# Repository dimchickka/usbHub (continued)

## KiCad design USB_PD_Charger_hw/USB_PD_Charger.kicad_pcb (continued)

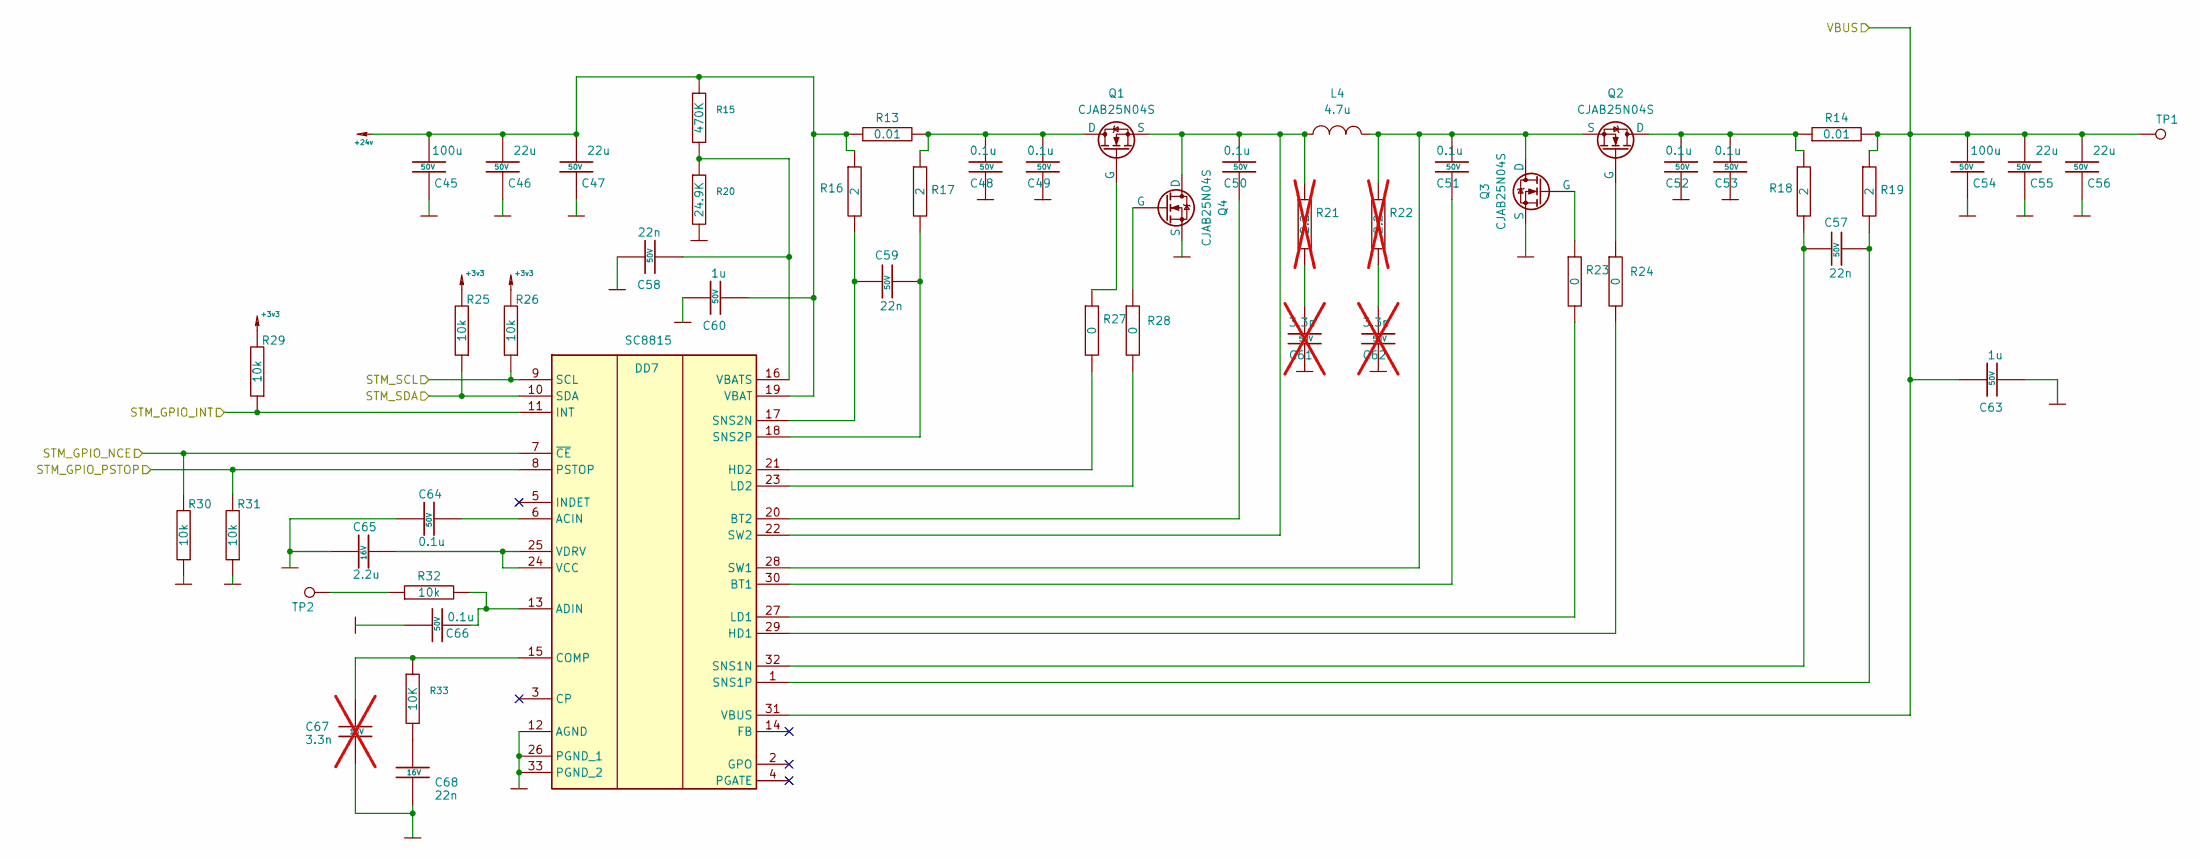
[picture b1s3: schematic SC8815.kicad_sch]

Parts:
C45, C54: 100u; CP_Elec_10x10.5_Pad2Plus; Tolerance 20%; Voltage 50V
C46, C47, C55, C56: 22u; CP_Elec_6.3x5.8_Pad2Plus; Tolerance 20%; Voltage 50V
C48, C49, C50, C51, C52, C53, C64, C66: 0.1u; CAP_0603_Silks; Tolerance 10%; Voltage 50V
C57, C58, C59: 22n; CAP_0603_Silks; Tolerance 5%; Voltage 50V
C60, C63: 1u; CAP_0603_Silks; Tolerance 10%; Voltage 50V
C61, C62: 3.3n; CAP_0603_Silks; Tolerance 10%; Voltage 50V; not fitted
C65: 2.2u; CAP_0603_Silks; Tolerance 10%; Voltage 16V
C67: 3.3n; CAP_0603_Silks; Tolerance 10%; Voltage 16V; not fitted
C68: 22n; CAP_0603_Silks; Tolerance 5%; Voltage 16V
DD7: SC8815; QFN40P400X400X80-33N-D; Manufacturer_Part_Number SC8815
L4: 4.7u; L_TaiTech_TMPC1265_13.5x12.5mm; Tolerance 20%
Q1, Q2, Q3, Q4: CJAB25N04S; CJAB25N04S_PDFNWB3.3x3.3-8L
R13, R14: 0.01; R_0805_2012Metric; Tolerance 1%
R15: 470K; RES_0603_Silks
R16, R17, R18, R19: 2; RES_0603_Silks; Tolerance 1%
R20: 24.9K; RES_0603_Silks
R21, R22: 2.2; RES_0603_Silks; Tolerance 1%; not fitted
R23, R24, R27, R28: 0; RES_0603_Silks; Tolerance 1%
R25, R26, R29, R30, R31, R32: 10k; RES_0603_Silks; Tolerance 1%
R33: 10K; RES_0603_Silks
TP1, TP2: TestPoint; TestPoint_Pad_D2.0mm

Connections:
+3v3: R25.2, R26.2, R29.2; also elsewhere on the board
+24v: C45.2, C46.2, C47.2, C60.2, DD7.19 (VBAT), R13.1, R15.1, R16.1; also elsewhere on the board
/Dual_USB_C_ports_1/STM_GPIO_INT1: DD7.11 (INT), R29.1; also elsewhere on the board
/Dual_USB_C_ports_1/STM_GPIO_NCE1: DD7.7 (~CE), R30.2; also elsewhere on the board
/Dual_USB_C_ports_1/STM_GPIO_PSTOP1: DD7.8 (PSTOP), R31.2; also elsewhere on the board
/Dual_USB_C_ports_1/STM_SCL1: DD7.9 (SCL), R26.1; also elsewhere on the board
/Dual_USB_C_ports_1/STM_SDA1: DD7.10 (SDA), R25.1; also elsewhere on the board
/Dual_USB_C_ports_1/VBUS_USB_CON_1: C54.2, C55.2, C56.2, C63.1, DD7.31 (VBUS), R14.2, R19.1, TP1.1; also elsewhere on the board
GND: C45.1, C46.1, C47.1, C48.2, C49.2, C52.2, C53.2, C54.1, C55.1, C56.1, C58.1, C60.1, C61.2, C62.2, C63.2, C64.2, C65.2, C66.1, C67.2, C68.2, DD7.12 (AGND), DD7.26 (PGND_1), DD7.33 (PGND_2), Q3.3 (S), Q4.3 (S), R20.2, R30.1, R31.1; also elsewhere on the board
unnamed: C61.1, R21.2
unnamed: C62.1, R22.2
unnamed: C68.1, R33.2
unnamed: C64.1, DD7.6 (ACIN)
unnamed: C66.2, DD7.13 (ADIN), R32.2
unnamed: C51.2, DD7.30 (BT1)
unnamed: C50.2, DD7.20 (BT2)
unnamed: C67.1, DD7.15 (COMP), R33.1
unnamed: DD7.29 (HD1), R24.2
unnamed: DD7.21 (HD2), R27.2
unnamed: DD7.27 (LD1), R23.2
unnamed: DD7.23 (LD2), R28.2
unnamed: C57.2, DD7.32 (SNS1N), R18.2
unnamed: C57.1, DD7.1 (SNS1P), R19.2
unnamed: C59.2, DD7.17 (SNS2N), R16.2
unnamed: C59.1, DD7.18 (SNS2P), R17.2
unnamed: C51.1, DD7.28 (SW1), L4.1, Q2.3 (S), Q3.1 (D), R22.1
unnamed: C50.1, DD7.22 (SW2), L4.2, Q1.3 (S), Q4.1 (D), R21.1
unnamed: C58.2, DD7.16 (VBATS), R15.2, R20.1
unnamed: C65.1, DD7.24 (VCC), DD7.25 (VDRV)
unnamed: C48.1, C49.1, Q1.1 (D), R13.2, R17.1
unnamed: Q1.2 (G), R27.1
unnamed: C52.1, C53.1, Q2.1 (D), R14.1, R18.1
unnamed: Q2.2 (G), R24.1
unnamed: Q3.2 (G), R23.1
unnamed: Q4.2 (G), R28.1
unnamed: R32.1, TP2.1

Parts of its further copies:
C69, C78, C95, C104, C119, C128, C145, C154, C169, C178, C195, C204, C219, C228, C245, C254, C269, C278, C295, C304, C319, C328, C345, C354, C369, C378, C395, C404, C419, C428, C445, C454, C469, C478, C495, C504, C519, C528: 100u; CP_Elec_10x10.5_Pad2Plus; Tolerance 20%; Voltage 50V
C70, C71, C79, C80, C96, C97, C105, C106, C120, C121, C129, C130, C146, C147, C155, C156, C170, C171, C179, C180, C196, C197, C205, C206, C220, C221, C229, C230, C246, C247, C255, C256, C270, C271, C279, C280, C296, C297, C305, C306, C320, C321, C329, C330, C346, C347, C355, C356, C370, C371, C379, C380, C396, C397, C405, C406, C420, C421, C429, C430, C446, C447, C455, C456, C470, C471, C479, C480, C496, C497, C505, C506, C520, C521, C529, C530: 22u; CP_Elec_6.3x5.8_Pad2Plus; Tolerance 20%; Voltage 50V
C72, C73, C74, C75, C76, C77, C88, C90, C98, C99, C100, C101, C102, C103, C114, C116, C122, C123, C124, C125, C126, C127, C138, C140, C148, C149, C150, C151, C152, C153, C164, C166, C172, C173, C174, C175, C176, C177, C188, C190, C198, C199, C200, C201, C202, C203, C214, C216, C222, C223, C224, C225, C226, C227, C238, C240, C248, C249, C250, C251, C252, C253, C264, C266, C272, C273, C274, C275, C276, C277, C288, C290, C298, C299, C300, C301, C302, C303, C314, C316, C322, C323, C324, C325, C326, C327, C338, C340, C348, C349, C350, C351, C352, C353, C364, C366, C372, C373, C374, C375, C376, C377, C388, C390, C398, C399, C400, C401, C402, C403, C414, C416, C422, C423, C424, C425, C426, C427, C438, C440, C448, C449, C450, C451, C452, C453, C464, C466, C472, C473, C474, C475, C476, C477, C488, C490, C498, C499, C500, C501, C502, C503, C514, C516, C522, C523, C524, C525, C526, C527, C538, C540: 0.1u; CAP_0603_Silks; Tolerance 10%; Voltage 50V
C81, C82, C83, C107, C108, C109, C131, C132, C133, C157, C158, C159, C181, C182, C183, C207, C208, C209, C231, C232, C233, C257, C258, C259, C281, C282, C283, C307, C308, C309, C331, C332, C333, C357, C358, C359, C381, C382, C383, C407, C408, C409, C431, C432, C433, C457, C458, C459, C481, C482, C483, C507, C508, C509, C531, C532, C533: 22n; CAP_0603_Silks; Tolerance 5%; Voltage 50V
C84, C87, C110, C113, C134, C137, C160, C163, C184, C187, C210, C213, C234, C237, C260, C263, C284, C287, C310, C313, C334, C337, C360, C363, C384, C387, C410, C413, C434, C437, C460, C463, C484, C487, C510, C513, C534, C537: 1u; CAP_0603_Silks; Tolerance 10%; Voltage 50V
C85, C86, C111, C112, C135, C136, C161, C162, C185, C186, C211, C212, C235, C236, C261, C262, C285, C286, C311, C312, C335, C336, C361, C362, C385, C386, C411, C412, C435, C436, C461, C462, C485, C486, C511, C512, C535, C536: 3.3n; CAP_0603_Silks; Tolerance 10%; Voltage 50V; not fitted
C89, C115, C139, C165, C189, C215, C239, C265, C289, C315, C339, C365, C389, C415, C439, C465, C489, C515, C539: 2.2u; CAP_0603_Silks; Tolerance 10%; Voltage 16V
C91, C117, C141, C167, C191, C217, C241, C267, C291, C317, C341, C367, C391, C417, C441, C467, C491, C517, C541: 3.3n; CAP_0603_Silks; Tolerance 10%; Voltage 16V; not fitted
C92, C118, C142, C168, C192, C218, C242, C268, C292, C318, C342, C368, C392, C418, C442, C468, C492, C518, C542: 22n; CAP_0603_Silks; Tolerance 5%; Voltage 16V
DD8, DD12, DD13, DD17, DD18, DD22, DD23, DD27, DD28, DD32, DD33, DD37, DD38, DD42, DD43, DD47, DD48, DD52, DD53: SC8815; QFN40P400X400X80-33N-D; Manufacturer_Part_Number SC8815
L5, L6, L7, L8, L9, L10, L11, L12, L13, L14, L15, L16, L17, L18, L19, L20, L21, L22, L23: 4.7u; L_TaiTech_TMPC1265_13.5x12.5mm; Tolerance 20%
Q5, Q6, Q7, Q8, Q9, Q10, Q11, Q12, Q13, Q14, Q15, Q16, Q17, Q18, Q19, Q20, Q21, Q22, Q23, Q24, Q25, Q26, Q27, Q28, Q29, Q30, Q31, Q32, Q33, Q34, Q35, Q36, Q37, Q38, Q39, Q40, Q41, Q42, Q43, Q44, Q45, Q46, Q47, Q48, Q49, Q50, Q51, Q52, Q53, Q54, Q55, Q56, Q57, Q58, Q59, Q60, Q61, Q62, Q63, Q64, Q65, Q66, Q67, Q68, Q69, Q70, Q71, Q72, Q73, Q74, Q75, Q76, Q77, Q78, Q79, Q80: CJAB25N04S; CJAB25N04S_PDFNWB3.3x3.3-8L
R34, R35, R57, R58, R78, R79, R101, R102, R122, R123, R145, R146, R166, R167, R189, R190, R210, R211, R233, R234, R254, R255, R277, R278, R298, R299, R321, R322, R342, R343, R365, R366, R386, R387, R409, R410, R430, R431: 0.01; R_0805_2012Metric; Tolerance 1%
R36, R59, R80, R103, R124, R147, R168, R191, R212, R235, R256, R279, R300, R323, R344, R367, R388, R411, R432: 470K; RES_0603_Silks
R37, R38, R39, R40, R60, R61, R62, R63, R81, R82, R83, R84, R104, R105, R106, R107, R125, R126, R127, R128, R148, R149, R150, R151, R169, R170, R171, R172, R192, R193, R194, R195, R213, R214, R215, R216, R236, R237, R238, R239, R257, R258, R259, R260, R280, R281, R282, R283, R301, R302, R303, R304, R324, R325, R326, R327, R345, R346, R347, R348, R368, R369, R370, R371, R389, R390, R391, R392, R412, R413, R414, R415, R433, R434, R435, R436: 2; RES_0603_Silks; Tolerance 1%
R41, R64, R85, R108, R129, R152, R173, R196, R217, R240, R261, R284, R305, R328, R349, R372, R393, R416, R437: 24.9K; RES_0603_Silks
R42, R43, R65, R66, R86, R87, R109, R110, R130, R131, R153, R154, R174, R175, R197, R198, R218, R219, R241, R242, R262, R263, R285, R286, R306, R307, R329, R330, R350, R351, R373, R374, R394, R395, R417, R418, R438, R439: 2.2; RES_0603_Silks; Tolerance 1%; not fitted
R44, R45, R48, R49, R67, R68, R71, R72, R88, R89, R92, R93, R111, R112, R115, R116, R132, R133, R136, R137, R155, R156, R159, R160, R176, R177, R180, R181, R199, R200, R203, R204, R220, R221, R224, R225, R243, R244, R247, R248, R264, R265, R268, R269, R287, R288, R291, R292, R308, R309, R312, R313, R331, R332, R335, R336, R352, R353, R356, R357, R375, R376, R379, R380, R396, R397, R400, R401, R419, R420, R423, R424, R440, R441, R444, R445: 0; RES_0603_Silks; Tolerance 1%
R46, R47, R50, R51, R52, R53, R69, R70, R73, R74, R75, R76, R90, R91, R94, R95, R96, R97, R113, R114, R117, R118, R119, R120, R134, R135, R138, R139, R140, R141, R157, R158, R161, R162, R163, R164, R178, R179, R182, R183, R184, R185, R201, R202, R205, R206, R207, R208, R222, R223, R226, R227, R228, R229, R245, R246, R249, R250, R251, R252, R266, R267, R270, R271, R272, R273, R289, R290, R293, R294, R295, R296, R310, R311, R314, R315, R316, R317, R333, R334, R337, R338, R339, R340, R354, R355, R358, R359, R360, R361, R377, R378, R381, R382, R383, R384, R398, R399, R402, R403, R404, R405, R421, R422, R425, R426, R427, R428, R442, R443, R446, R447, R448, R449: 10k; RES_0603_Silks; Tolerance 1%
R54, R77, R98, R121, R142, R165, R186, R209, R230, R253, R274, R297, R318, R341, R362, R385, R406, R429, R450: 10K; RES_0603_Silks
TP3, TP4, TP5, TP6, TP7, TP8, TP9, TP10, TP11, TP12, TP13, TP14, TP15, TP16, TP17, TP18, TP19, TP20, TP21, TP22, TP23, TP24, TP25, TP26, TP27, TP28, TP29, TP30, TP31, TP32, TP33, TP34, TP35, TP36, TP37, TP38, TP39, TP40: TestPoint; TestPoint_Pad_D2.0mm

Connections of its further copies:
+3v3: R46.2, R47.2, R50.2, R69.2, R70.2, R73.2, R90.2, R91.2, R94.2, R113.2, R114.2, R117.2, R134.2, R135.2, R138.2, R157.2, R158.2, R161.2, R178.2, R179.2, R182.2, R201.2, R202.2, R205.2, R222.2, R223.2, R226.2, R245.2, R246.2, R249.2, R266.2, R267.2, R270.2, R289.2, R290.2, R293.2, R310.2, R311.2, R314.2, R333.2, R334.2, R337.2, R354.2, R355.2, R358.2, R377.2, R378.2, R381.2, R398.2, R399.2, R402.2, R421.2, R422.2, R425.2, R442.2, R443.2, R446.2; also elsewhere on the board
+24v: C69.2, C70.2, C71.2, C84.2, C95.2, C96.2, C97.2, C110.2, C119.2, C120.2, C121.2, C134.2, C145.2, C146.2, C147.2, C160.2, C169.2, C170.2, C171.2, C184.2, C195.2, C196.2, C197.2, C210.2, C219.2, C220.2, C221.2, C234.2, C245.2, C246.2, C247.2, C260.2, C269.2, C270.2, C271.2, C284.2, C295.2, C296.2, C297.2, C310.2, C319.2, C320.2, C321.2, C334.2, C345.2, C346.2, C347.2, C360.2, C369.2, C370.2, C371.2, C384.2, C395.2, C396.2, C397.2, C410.2, C419.2, C420.2, C421.2, C434.2, C445.2, C446.2, C447.2, C460.2, C469.2, C470.2, C471.2, C484.2, C495.2, C496.2, C497.2, C510.2, C519.2, C520.2, C521.2, C534.2, DD8.19 (VBAT), DD12.19 (VBAT), DD13.19 (VBAT), DD17.19 (VBAT), DD18.19 (VBAT), DD22.19 (VBAT), DD23.19 (VBAT), DD27.19 (VBAT), DD28.19 (VBAT), DD32.19 (VBAT), DD33.19 (VBAT), DD37.19 (VBAT), DD38.19 (VBAT), DD42.19 (VBAT), DD43.19 (VBAT), DD47.19 (VBAT), DD48.19 (VBAT), DD52.19 (VBAT), DD53.19 (VBAT), R34.1, R36.1, R37.1, R57.1, R59.1, R60.1, R78.1, R80.1, R81.1, R101.1, R103.1, R104.1, R122.1, R124.1, R125.1, R145.1, R147.1, R148.1, R166.1, R168.1, R169.1, R189.1, R191.1, R192.1, R210.1, R212.1, R213.1, R233.1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; also elsewhere on the board
/Dual_USB_C_ports_1/STM_GPIO_INT2: DD8.11 (INT), R50.1; also elsewhere on the board
/Dual_USB_C_ports_1/STM_GPIO_NCE2: DD8.7 (~CE), R51.2; also elsewhere on the board
/Dual_USB_C_ports_1/STM_GPIO_PSTOP2: DD8.8 (PSTOP), R52.2; also elsewhere on the board
/Dual_USB_C_ports_1/STM_SCL2: DD8.9 (SCL), R47.1; also elsewhere on the board
/Dual_USB_C_ports_1/STM_SDA2: DD8.10 (SDA), R46.1; also elsewhere on the board
/Dual_USB_C_ports_1/VBUS_USB_CON_2: C78.2, C79.2, C80.2, C87.1, DD8.31 (VBUS), R35.2, R40.1, TP3.1; also elsewhere on the board
/Dual_USB_C_ports_2/STM_GPIO_INT1: DD12.11 (INT), R73.1; also elsewhere on the board
/Dual_USB_C_ports_2/STM_GPIO_INT2: DD13.11 (INT), R94.1; also elsewhere on the board
/Dual_USB_C_ports_2/STM_GPIO_NCE1: DD12.7 (~CE), R74.2; also elsewhere on the board
/Dual_USB_C_ports_2/STM_GPIO_NCE2: DD13.7 (~CE), R95.2; also elsewhere on the board
/Dual_USB_C_ports_2/STM_GPIO_PSTOP1: DD12.8 (PSTOP), R75.2; also elsewhere on the board
/Dual_USB_C_ports_2/STM_GPIO_PSTOP2: DD13.8 (PSTOP), R96.2; also elsewhere on the board
/Dual_USB_C_ports_2/STM_SCL1: DD12.9 (SCL), R70.1; also elsewhere on the board
/Dual_USB_C_ports_2/STM_SCL2: DD13.9 (SCL), R91.1; also elsewhere on the board
/Dual_USB_C_ports_2/STM_SDA1: DD12.10 (SDA), R69.1; also elsewhere on the board
/Dual_USB_C_ports_2/STM_SDA2: DD13.10 (SDA), R90.1; also elsewhere on the board
/Dual_USB_C_ports_2/VBUS_USB_CON_1: C104.2, C105.2, C106.2, C113.1, DD12.31 (VBUS), R58.2, R63.1, TP5.1; also elsewhere on the board
/Dual_USB_C_ports_2/VBUS_USB_CON_2: C128.2, C129.2, C130.2, C137.1, DD13.31 (VBUS), R79.2, R84.1, TP7.1; also elsewhere on the board
/Dual_USB_C_ports_3/STM_GPIO_INT1: DD17.11 (INT), R117.1; also elsewhere on the board
/Dual_USB_C_ports_3/STM_GPIO_INT2: DD18.11 (INT), R138.1; also elsewhere on the board
/Dual_USB_C_ports_3/STM_GPIO_NCE1: DD17.7 (~CE), R118.2; also elsewhere on the board
/Dual_USB_C_ports_3/STM_GPIO_NCE2: DD18.7 (~CE), R139.2; also elsewhere on the board
/Dual_USB_C_ports_3/STM_GPIO_PSTOP1: DD17.8 (PSTOP), R119.2; also elsewhere on the board
/Dual_USB_C_ports_3/STM_GPIO_PSTOP2: DD18.8 (PSTOP), R140.2; also elsewhere on the board
/Dual_USB_C_ports_3/STM_SCL1: DD17.9 (SCL), R114.1; also elsewhere on the board
/Dual_USB_C_ports_3/STM_SCL2: DD18.9 (SCL), R135.1; also elsewhere on the board
/Dual_USB_C_ports_3/STM_SDA1: DD17.10 (SDA), R113.1; also elsewhere on the board
/Dual_USB_C_ports_3/STM_SDA2: DD18.10 (SDA), R134.1; also elsewhere on the board
/Dual_USB_C_ports_3/VBUS_USB_CON_1: C154.2, C155.2, C156.2, C163.1, DD17.31 (VBUS), R102.2, R107.1, TP9.1; also elsewhere on the board
/Dual_USB_C_ports_3/VBUS_USB_CON_2: C178.2, C179.2, C180.2, C187.1, DD18.31 (VBUS), R123.2, R128.1, TP11.1; also elsewhere on the board
/Dual_USB_C_ports_4/STM_GPIO_INT1: DD22.11 (INT), R161.1; also elsewhere on the board
/Dual_USB_C_ports_4/STM_GPIO_INT2: DD23.11 (INT), R182.1; also elsewhere on the board
/Dual_USB_C_ports_4/STM_GPIO_NCE1: DD22.7 (~CE), R162.2; also elsewhere on the board
/Dual_USB_C_ports_4/STM_GPIO_NCE2: DD23.7 (~CE), R183.2; also elsewhere on the board
/Dual_USB_C_ports_4/STM_GPIO_PSTOP1: DD22.8 (PSTOP), R163.2; also elsewhere on the board
/Dual_USB_C_ports_4/STM_GPIO_PSTOP2: DD23.8 (PSTOP), R184.2; also elsewhere on the board
/Dual_USB_C_ports_4/STM_SCL1: DD22.9 (SCL), R158.1; also elsewhere on the board
/Dual_USB_C_ports_4/STM_SCL2: DD23.9 (SCL), R179.1; also elsewhere on the board
/Dual_USB_C_ports_4/STM_SDA1: DD22.10 (SDA), R157.1; also elsewhere on the board
/Dual_USB_C_ports_4/STM_SDA2: DD23.10 (SDA), R178.1; also elsewhere on the board
/Dual_USB_C_ports_4/VBUS_USB_CON_1: C204.2, C205.2, C206.2, C213.1, DD22.31 (VBUS), R146.2, R151.1, TP13.1; also elsewhere on the board
/Dual_USB_C_ports_4/VBUS_USB_CON_2: C228.2, C229.2, C230.2, C237.1, DD23.31 (VBUS), R167.2, R172.1, TP15.1; also elsewhere on the board
/Dual_USB_C_ports_5/STM_GPIO_INT1: DD27.11 (INT), R205.1; also elsewhere on the board
/Dual_USB_C_ports_5/STM_GPIO_INT2: DD28.11 (INT), R226.1; also elsewhere on the board
/Dual_USB_C_ports_5/STM_GPIO_NCE1: DD27.7 (~CE), R206.2; also elsewhere on the board
/Dual_USB_C_ports_5/STM_GPIO_NCE2: DD28.7 (~CE), R227.2; also elsewhere on the board
/Dual_USB_C_ports_5/STM_GPIO_PSTOP1: DD27.8 (PSTOP), R207.2; also elsewhere on the board
/Dual_USB_C_ports_5/STM_GPIO_PSTOP2: DD28.8 (PSTOP), R228.2; also elsewhere on the board
/Dual_USB_C_ports_5/STM_SCL1: DD27.9 (SCL), R202.1; also elsewhere on the board
/Dual_USB_C_ports_5/STM_SCL2: DD28.9 (SCL), R223.1; also elsewhere on the board
/Dual_USB_C_ports_5/STM_SDA1: DD27.10 (SDA), R201.1; also elsewhere on the board
/Dual_USB_C_ports_5/STM_SDA2: DD28.10 (SDA), R222.1; also elsewhere on the board
/Dual_USB_C_ports_5/VBUS_USB_CON_1: C254.2, C255.2, C256.2, C263.1, DD27.31 (VBUS), R190.2, R195.1, TP17.1; also elsewhere on the board
/Dual_USB_C_ports_5/VBUS_USB_CON_2: C278.2, C279.2, C280.2, C287.1, DD28.31 (VBUS), R211.2, R216.1, TP19.1; also elsewhere on the board
/Dual_USB_C_ports_6/STM_GPIO_INT1: DD32.11 (INT), R249.1; also elsewhere on the board
/Dual_USB_C_ports_6/STM_GPIO_INT2: DD33.11 (INT), R270.1; also elsewhere on the board
/Dual_USB_C_ports_6/STM_GPIO_NCE1: DD32.7 (~CE), R250.2; also elsewhere on the board
/Dual_USB_C_ports_6/STM_GPIO_NCE2: DD33.7 (~CE), R271.2; also elsewhere on the board
/Dual_USB_C_ports_6/STM_GPIO_PSTOP1: DD32.8 (PSTOP), R251.2; also elsewhere on the board
/Dual_USB_C_ports_6/STM_GPIO_PSTOP2: DD33.8 (PSTOP), R272.2; also elsewhere on the board
/Dual_USB_C_ports_6/STM_SCL1: DD32.9 (SCL), R246.1; also elsewhere on the board
/Dual_USB_C_ports_6/STM_SCL2: DD33.9 (SCL), R267.1; also elsewhere on the board
/Dual_USB_C_ports_6/STM_SDA1: DD32.10 (SDA), R245.1; also elsewhere on the board
/Dual_USB_C_ports_6/STM_SDA2: DD33.10 (SDA), R266.1; also elsewhere on the board
/Dual_USB_C_ports_6/VBUS_USB_CON_1: C304.2, C305.2, C306.2, C313.1, DD32.31 (VBUS), R234.2, R239.1, TP21.1; also elsewhere on the board
/Dual_USB_C_ports_6/VBUS_USB_CON_2: C328.2, C329.2, C330.2, C337.1, DD33.31 (VBUS), R255.2, R260.1, TP23.1; also elsewhere on the board
/Dual_USB_C_ports_7/STM_GPIO_INT1: DD37.11 (INT), R293.1; also elsewhere on the board
/Dual_USB_C_ports_7/STM_GPIO_INT2: DD38.11 (INT), R314.1; also elsewhere on the board
/Dual_USB_C_ports_7/STM_GPIO_NCE1: DD37.7 (~CE), R294.2; also elsewhere on the board
/Dual_USB_C_ports_7/STM_GPIO_NCE2: DD38.7 (~CE), R315.2; also elsewhere on the board
/Dual_USB_C_ports_7/STM_GPIO_PSTOP1: DD37.8 (PSTOP), R295.2; also elsewhere on the board
/Dual_USB_C_ports_7/STM_GPIO_PSTOP2: DD38.8 (PSTOP), R316.2; also elsewhere on the board
/Dual_USB_C_ports_7/STM_SCL1: DD37.9 (SCL), R290.1; also elsewhere on the board
/Dual_USB_C_ports_7/STM_SCL2: DD38.9 (SCL), R311.1; also elsewhere on the board
/Dual_USB_C_ports_7/STM_SDA1: DD37.10 (SDA), R289.1; also elsewhere on the board
/Dual_USB_C_ports_7/STM_SDA2: DD38.10 (SDA), R310.1; also elsewhere on the board
/Dual_USB_C_ports_7/VBUS_USB_CON_1: C354.2, C355.2, C356.2, C363.1, DD37.31 (VBUS), R278.2, R283.1, TP25.1; also elsewhere on the board
/Dual_USB_C_ports_7/VBUS_USB_CON_2: C378.2, C379.2, C380.2, C387.1, DD38.31 (VBUS), R299.2, R304.1, TP27.1; also elsewhere on the board
/Dual_USB_C_ports_8/STM_GPIO_INT1: DD42.11 (INT), R337.1; also elsewhere on the board
/Dual_USB_C_ports_8/STM_GPIO_INT2: DD43.11 (INT), R358.1; also elsewhere on the board
/Dual_USB_C_ports_8/STM_GPIO_NCE1: DD42.7 (~CE), R338.2; also elsewhere on the board
/Dual_USB_C_ports_8/STM_GPIO_NCE2: DD43.7 (~CE), R359.2; also elsewhere on the board
/Dual_USB_C_ports_8/STM_GPIO_PSTOP1: DD42.8 (PSTOP), R339.2; also elsewhere on the board
/Dual_USB_C_ports_8/STM_GPIO_PSTOP2: DD43.8 (PSTOP), R360.2; also elsewhere on the board
/Dual_USB_C_ports_8/STM_SCL1: DD42.9 (SCL), R334.1; also elsewhere on the board
/Dual_USB_C_ports_8/STM_SCL2: DD43.9 (SCL), R355.1; also elsewhere on the board
/Dual_USB_C_ports_8/STM_SDA1: DD42.10 (SDA), R333.1; also elsewhere on the board
/Dual_USB_C_ports_8/STM_SDA2: DD43.10 (SDA), R354.1; also elsewhere on the board
/Dual_USB_C_ports_8/VBUS_USB_CON_1: C404.2, C405.2, C406.2, C413.1, DD42.31 (VBUS), R322.2, R327.1, TP29.1; also elsewhere on the board
/Dual_USB_C_ports_8/VBUS_USB_CON_2: C428.2, C429.2, C430.2, C437.1, DD43.31 (VBUS), R343.2, R348.1, TP31.1; also elsewhere on the board
/Dual_USB_C_ports_9/STM_GPIO_INT1: DD47.11 (INT), R381.1; also elsewhere on the board
/Dual_USB_C_ports_9/STM_GPIO_INT2: DD48.11 (INT), R402.1; also elsewhere on the board
/Dual_USB_C_ports_9/STM_GPIO_NCE1: DD47.7 (~CE), R382.2; also elsewhere on the board
/Dual_USB_C_ports_9/STM_GPIO_NCE2: DD48.7 (~CE), R403.2; also elsewhere on the board
/Dual_USB_C_ports_9/STM_GPIO_PSTOP1: DD47.8 (PSTOP), R383.2; also elsewhere on the board
/Dual_USB_C_ports_9/STM_GPIO_PSTOP2: DD48.8 (PSTOP), R404.2; also elsewhere on the board
/Dual_USB_C_ports_9/STM_SCL1: DD47.9 (SCL), R378.1; also elsewhere on the board
/Dual_USB_C_ports_9/STM_SCL2: DD48.9 (SCL), R399.1; also elsewhere on the board
/Dual_USB_C_ports_9/STM_SDA1: DD47.10 (SDA), R377.1; also elsewhere on the board
/Dual_USB_C_ports_9/STM_SDA2: DD48.10 (SDA), R398.1; also elsewhere on the board
/Dual_USB_C_ports_9/VBUS_USB_CON_1: C454.2, C455.2, C456.2, C463.1, DD47.31 (VBUS), R366.2, R371.1, TP33.1; also elsewhere on the board
/Dual_USB_C_ports_9/VBUS_USB_CON_2: C478.2, C479.2, C480.2, C487.1, DD48.31 (VBUS), R387.2, R392.1, TP35.1; also elsewhere on the board
/Dual_USB_C_ports_10/STM_GPIO_INT1: DD52.11 (INT), R425.1; also elsewhere on the board
/Dual_USB_C_ports_10/STM_GPIO_INT2: DD53.11 (INT), R446.1; also elsewhere on the board
/Dual_USB_C_ports_10/STM_GPIO_NCE1: DD52.7 (~CE), R426.2; also elsewhere on the board
/Dual_USB_C_ports_10/STM_GPIO_NCE2: DD53.7 (~CE), R447.2; also elsewhere on the board
/Dual_USB_C_ports_10/STM_GPIO_PSTOP1: DD52.8 (PSTOP), R427.2; also elsewhere on the board
/Dual_USB_C_ports_10/STM_GPIO_PSTOP2: DD53.8 (PSTOP), R448.2; also elsewhere on the board
/Dual_USB_C_ports_10/STM_SCL1: DD52.9 (SCL), R422.1; also elsewhere on the board
/Dual_USB_C_ports_10/STM_SCL2: DD53.9 (SCL), R443.1; also elsewhere on the board
/Dual_USB_C_ports_10/STM_SDA1: DD52.10 (SDA), R421.1; also elsewhere on the board
/Dual_USB_C_ports_10/STM_SDA2: DD53.10 (SDA), R442.1; also elsewhere on the board
/Dual_USB_C_ports_10/VBUS_USB_CON_1: C504.2, C505.2, C506.2, C513.1, DD52.31 (VBUS), R410.2, R415.1, TP37.1; also elsewhere on the board
/Dual_USB_C_ports_10/VBUS_USB_CON_2: C528.2, C529.2, C530.2, C537.1, DD53.31 (VBUS), R431.2, R436.1, TP39.1; also elsewhere on the board
GND: C69.1, C70.1, C71.1, C72.2, C73.2, C76.2, C77.2, C78.1, C79.1, C80.1, C82.1, C84.1, C85.2, C86.2, C87.2, C88.2, C89.2, C90.1, C91.2, C92.2, C95.1, C96.1, C97.1, C98.2, C99.2, C102.2, C103.2, C104.1, C105.1, C106.1, C108.1, C110.1, C111.2, C112.2, C113.2, C114.2, C115.2, C116.1, C117.2, C118.2, C119.1, C120.1, C121.1, C122.2, C123.2, C126.2, C127.2, C128.1, C129.1, C130.1, C132.1, C134.1, C135.2, C136.2, C137.2, C138.2, C139.2, C140.1, C141.2, C142.2, C145.1, C146.1, C147.1, C148.2, C149.2, C152.2, C153.2, C154.1, C155.1, C156.1, C158.1, C160.1, C161.2, C162.2, C163.2, C164.2, C165.2, C166.1, C167.2, C168.2, C169.1, C170.1, C171.1, C172.2, C173.2, C176.2, C177.2, C178.1, C179.1, C180.1, C182.1, C184.1, C185.2, C186.2, C187.2, C188.2, C189.2, C190.1, C191.2, C192.2, C195.1, C196.1, C197.1, C198.2, C199.2, C202.2, C203.2, C204.1, C205.1, C206.1, C208.1, C210.1, C211.2, C212.2, C213.2, C214.2, C215.2, C216.1, C217.2, C218.2, C219.1, C220.1, C221.1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; also elsewhere on the board
unnamed: C85.1, R42.2
unnamed: C86.1, R43.2
unnamed: C92.1, R54.2
unnamed: C111.1, R65.2
unnamed: C112.1, R66.2
unnamed: C118.1, R77.2
unnamed: C135.1, R86.2
unnamed: C136.1, R87.2
unnamed: C142.1, R98.2
unnamed: C161.1, R109.2
unnamed: C162.1, R110.2
unnamed: C168.1, R121.2
unnamed: C185.1, R130.2
unnamed: C186.1, R131.2
unnamed: C192.1, R142.2
unnamed: C211.1, R153.2
unnamed: C212.1, R154.2
unnamed: C218.1, R165.2
unnamed: C235.1, R174.2
unnamed: C236.1, R175.2
unnamed: C242.1, R186.2
unnamed: C261.1, R197.2
unnamed: C262.1, R198.2
unnamed: C268.1, R209.2
unnamed: C285.1, R218.2
unnamed: C286.1, R219.2
unnamed: C292.1, R230.2
unnamed: C311.1, R241.2
unnamed: C312.1, R242.2
unnamed: C318.1, R253.2
unnamed: C335.1, R262.2
unnamed: C336.1, R263.2
unnamed: C342.1, R274.2
unnamed: C361.1, R285.2
unnamed: C362.1, R286.2
unnamed: C368.1, R297.2
unnamed: C385.1, R306.2
unnamed: C386.1, R307.2
unnamed: C392.1, R318.2
unnamed: C411.1, R329.2
unnamed: C412.1, R330.2
unnamed: C418.1, R341.2
unnamed: C435.1, R350.2
unnamed: C436.1, R351.2
unnamed: C442.1, R362.2
unnamed: C461.1, R373.2
unnamed: C462.1, R374.2
unnamed: C468.1, R385.2
unnamed: C485.1, R394.2
unnamed: C486.1, R395.2
unnamed: C492.1, R406.2
unnamed: C511.1, R417.2
unnamed: C512.1, R418.2
unnamed: C518.1, R429.2
unnamed: C535.1, R438.2
unnamed: C536.1, R439.2
unnamed: C542.1, R450.2
unnamed: C88.1, DD8.6 (ACIN)
unnamed: C90.2, DD8.13 (ADIN), R53.2
unnamed: C75.2, DD8.30 (BT1)
unnamed: C74.2, DD8.20 (BT2)
unnamed: C91.1, DD8.15 (COMP), R54.1
unnamed: DD8.29 (HD1), R45.2
unnamed: DD8.21 (HD2), R48.2
unnamed: DD8.27 (LD1), R44.2
unnamed: DD8.23 (LD2), R49.2
unnamed: C81.2, DD8.32 (SNS1N), R39.2
unnamed: C81.1, DD8.1 (SNS1P), R40.2
unnamed: C83.2, DD8.17 (SNS2N), R37.2
unnamed: C83.1, DD8.18 (SNS2P), R38.2
unnamed: C75.1, DD8.28 (SW1), L5.1, Q6.3 (S), Q7.1 (D), R43.1
unnamed: C74.1, DD8.22 (SW2), L5.2, Q5.3 (S), Q8.1 (D), R42.1
unnamed: C82.2, DD8.16 (VBATS), R36.2, R41.1
unnamed: C89.1, DD8.24 (VCC), DD8.25 (VDRV)
unnamed: C114.1, DD12.6 (ACIN)
unnamed: C116.2, DD12.13 (ADIN), R76.2
unnamed: C101.2, DD12.30 (BT1)
unnamed: C100.2, DD12.20 (BT2)
unnamed: C117.1, DD12.15 (COMP), R77.1
unnamed: DD12.29 (HD1), R68.2
unnamed: DD12.21 (HD2), R71.2
unnamed: DD12.27 (LD1), R67.2
unnamed: DD12.23 (LD2), R72.2
unnamed: C107.2, DD12.32 (SNS1N), R62.2
unnamed: C107.1, DD12.1 (SNS1P), R63.2
unnamed: C109.2, DD12.17 (SNS2N), R60.2
unnamed: C109.1, DD12.18 (SNS2P), R61.2
unnamed: C101.1, DD12.28 (SW1), L6.1, Q10.3 (S), Q11.1 (D), R66.1
unnamed: C100.1, DD12.22 (SW2), L6.2, Q9.3 (S), Q12.1 (D), R65.1
unnamed: C108.2, DD12.16 (VBATS), R59.2, R64.1
unnamed: C115.1, DD12.24 (VCC), DD12.25 (VDRV)
unnamed: C138.1, DD13.6 (ACIN)
unnamed: C140.2, DD13.13 (ADIN), R97.2
unnamed: C125.2, DD13.30 (BT1)
unnamed: C124.2, DD13.20 (BT2)
unnamed: C141.1, DD13.15 (COMP), R98.1
unnamed: DD13.29 (HD1), R89.2
unnamed: DD13.21 (HD2), R92.2
unnamed: DD13.27 (LD1), R88.2
unnamed: DD13.23 (LD2), R93.2
unnamed: C131.2, DD13.32 (SNS1N), R83.2
unnamed: C131.1, DD13.1 (SNS1P), R84.2
unnamed: C133.2, DD13.17 (SNS2N), R81.2
unnamed: C133.1, DD13.18 (SNS2P), R82.2
unnamed: C125.1, DD13.28 (SW1), L7.1, Q14.3 (S), Q15.1 (D), R87.1
unnamed: C124.1, DD13.22 (SW2), L7.2, Q13.3 (S), Q16.1 (D), R86.1
unnamed: C132.2, DD13.16 (VBATS), R80.2, R85.1
unnamed: C139.1, DD13.24 (VCC), DD13.25 (VDRV)
unnamed: C164.1, DD17.6 (ACIN)
unnamed: C166.2, DD17.13 (ADIN), R120.2
unnamed: C151.2, DD17.30 (BT1)
unnamed: C150.2, DD17.20 (BT2)
unnamed: C167.1, DD17.15 (COMP), R121.1
unnamed: DD17.29 (HD1), R112.2
unnamed: DD17.21 (HD2), R115.2
unnamed: DD17.27 (LD1), R111.2
unnamed: DD17.23 (LD2), R116.2
unnamed: C157.2, DD17.32 (SNS1N), R106.2
unnamed: C157.1, DD17.1 (SNS1P), R107.2
unnamed: C159.2, DD17.17 (SNS2N), R104.2
unnamed: C159.1, DD17.18 (SNS2P), R105.2
unnamed: C151.1, DD17.28 (SW1), L8.1, Q18.3 (S), Q19.1 (D), R110.1
unnamed: C150.1, DD17.22 (SW2), L8.2, Q17.3 (S), Q20.1 (D), R109.1
unnamed: C158.2, DD17.16 (VBATS), R103.2, R108.1
unnamed: C165.1, DD17.24 (VCC), DD17.25 (VDRV)
unnamed: C188.1, DD18.6 (ACIN)
unnamed: C190.2, DD18.13 (ADIN), R141.2
unnamed: C175.2, DD18.30 (BT1)
unnamed: C174.2, DD18.20 (BT2)
unnamed: C191.1, DD18.15 (COMP), R142.1
unnamed: DD18.29 (HD1), R133.2
unnamed: DD18.21 (HD2), R136.2
unnamed: DD18.27 (LD1), R132.2
unnamed: DD18.23 (LD2), R137.2
unnamed: C181.2, DD18.32 (SNS1N), R127.2
unnamed: C181.1, DD18.1 (SNS1P), R128.2
unnamed: C183.2, DD18.17 (SNS2N), R125.2
unnamed: C183.1, DD18.18 (SNS2P), R126.2
unnamed: C175.1, DD18.28 (SW1), L9.1, Q22.3 (S), Q23.1 (D), R131.1
unnamed: C174.1, DD18.22 (SW2), L9.2, Q21.3 (S), Q24.1 (D), R130.1
unnamed: C182.2, DD18.16 (VBATS), R124.2, R129.1
unnamed: C189.1, DD18.24 (VCC), DD18.25 (VDRV)
unnamed: C214.1, DD22.6 (ACIN)
unnamed: C216.2, DD22.13 (ADIN), R164.2
unnamed: C201.2, DD22.30 (BT1)
unnamed: C200.2, DD22.20 (BT2)
unnamed: C217.1, DD22.15 (COMP), R165.1
unnamed: DD22.29 (HD1), R156.2
unnamed: DD22.21 (HD2), R159.2
unnamed: DD22.27 (LD1), R155.2
unnamed: DD22.23 (LD2), R160.2
unnamed: C207.2, DD22.32 (SNS1N), R150.2
unnamed: C207.1, DD22.1 (SNS1P), R151.2
unnamed: C209.2, DD22.17 (SNS2N), R148.2
unnamed: C209.1, DD22.18 (SNS2P), R149.2
unnamed: C201.1, DD22.28 (SW1), L10.1, Q26.3 (S), Q27.1 (D), R154.1
unnamed: C200.1, DD22.22 (SW2), L10.2, Q25.3 (S), Q28.1 (D), R153.1
unnamed: C208.2, DD22.16 (VBATS), R147.2, R152.1
unnamed: C215.1, DD22.24 (VCC), DD22.25 (VDRV)
unnamed: C238.1, DD23.6 (ACIN)
unnamed: C240.2, DD23.13 (ADIN), R185.2
unnamed: C225.2, DD23.30 (BT1)
unnamed: C224.2, DD23.20 (BT2)
unnamed: C241.1, DD23.15 (COMP), R186.1
unnamed: DD23.29 (HD1), R177.2
unnamed: DD23.21 (HD2), R180.2
unnamed: DD23.27 (LD1), R176.2
unnamed: DD23.23 (LD2), R181.2
unnamed: C231.2, DD23.32 (SNS1N), R171.2
unnamed: C231.1, DD23.1 (SNS1P), R172.2
unnamed: C233.2, DD23.17 (SNS2N), R169.2
unnamed: C233.1, DD23.18 (SNS2P), R170.2
unnamed: C225.1, DD23.28 (SW1), L11.1, Q30.3 (S), Q31.1 (D), R175.1
unnamed: C224.1, DD23.22 (SW2), L11.2, Q29.3 (S), Q32.1 (D), R174.1
unnamed: C232.2, DD23.16 (VBATS), R168.2, R173.1
unnamed: C239.1, DD23.24 (VCC), DD23.25 (VDRV)
unnamed: C264.1, DD27.6 (ACIN)
unnamed: C266.2, DD27.13 (ADIN), R208.2
unnamed: C251.2, DD27.30 (BT1)
unnamed: C250.2, DD27.20 (BT2)
unnamed: C267.1, DD27.15 (COMP), R209.1
unnamed: DD27.29 (HD1), R200.2
unnamed: DD27.21 (HD2), R203.2
unnamed: DD27.27 (LD1), R199.2
unnamed: DD27.23 (LD2), R204.2
unnamed: C257.2, DD27.32 (SNS1N), R194.2
unnamed: C257.1, DD27.1 (SNS1P), R195.2
unnamed: C259.2, DD27.17 (SNS2N), R192.2
unnamed: C259.1, DD27.18 (SNS2P), R193.2
unnamed: C251.1, DD27.28 (SW1), L12.1, Q34.3 (S), Q35.1 (D), R198.1
unnamed: C250.1, DD27.22 (SW2), L12.2, Q33.3 (S), Q36.1 (D), R197.1
unnamed: C258.2, DD27.16 (VBATS), R191.2, R196.1
unnamed: C265.1, DD27.24 (VCC), DD27.25 (VDRV)
unnamed: C288.1, DD28.6 (ACIN)
unnamed: C290.2, DD28.13 (ADIN), R229.2
unnamed: C275.2, DD28.30 (BT1)
unnamed: C274.2, DD28.20 (BT2)
unnamed: C291.1, DD28.15 (COMP), R230.1
unnamed: DD28.29 (HD1), R221.2
unnamed: DD28.21 (HD2), R224.2
unnamed: DD28.27 (LD1), R220.2
unnamed: DD28.23 (LD2), R225.2
unnamed: C281.2, DD28.32 (SNS1N), R215.2
unnamed: C281.1, DD28.1 (SNS1P), R216.2
unnamed: C283.2, DD28.17 (SNS2N), R213.2
unnamed: C283.1, DD28.18 (SNS2P), R214.2
unnamed: C275.1, DD28.28 (SW1), L13.1, Q38.3 (S), Q39.1 (D), R219.1
unnamed: C274.1, DD28.22 (SW2), L13.2, Q37.3 (S), Q40.1 (D), R218.1
unnamed: C282.2, DD28.16 (VBATS), R212.2, R217.1
unnamed: C289.1, DD28.24 (VCC), DD28.25 (VDRV)
unnamed: C314.1, DD32.6 (ACIN)
unnamed: C316.2, DD32.13 (ADIN), R252.2
unnamed: C301.2, DD32.30 (BT1)
unnamed: C300.2, DD32.20 (BT2)
unnamed: C317.1, DD32.15 (COMP), R253.1
unnamed: DD32.29 (HD1), R244.2
unnamed: DD32.21 (HD2), R247.2
unnamed: DD32.27 (LD1), R243.2
unnamed: DD32.23 (LD2), R248.2
unnamed: C307.2, DD32.32 (SNS1N), R238.2
unnamed: C307.1, DD32.1 (SNS1P), R239.2
unnamed: C309.2, DD32.17 (SNS2N), R236.2
unnamed: C309.1, DD32.18 (SNS2P), R237.2
unnamed: C301.1, DD32.28 (SW1), L14.1, Q42.3 (S), Q43.1 (D), R242.1
unnamed: C300.1, DD32.22 (SW2), L14.2, Q41.3 (S), Q44.1 (D), R241.1
unnamed: C308.2, DD32.16 (VBATS), R235.2, R240.1
unnamed: C315.1, DD32.24 (VCC), DD32.25 (VDRV)
unnamed: C338.1, DD33.6 (ACIN)
unnamed: C340.2, DD33.13 (ADIN), R273.2
unnamed: C325.2, DD33.30 (BT1)
unnamed: C324.2, DD33.20 (BT2)
unnamed: C341.1, DD33.15 (COMP), R274.1
unnamed: DD33.29 (HD1), R265.2
unnamed: DD33.21 (HD2), R268.2
unnamed: DD33.27 (LD1), R264.2
unnamed: DD33.23 (LD2), R269.2
unnamed: C331.2, DD33.32 (SNS1N), R259.2
unnamed: C331.1, DD33.1 (SNS1P), R260.2
unnamed: C333.2, DD33.17 (SNS2N), R257.2
unnamed: C333.1, DD33.18 (SNS2P), R258.2
unnamed: C325.1, DD33.28 (SW1), L15.1, Q46.3 (S), Q47.1 (D), R263.1
unnamed: C324.1, DD33.22 (SW2), L15.2, Q45.3 (S), Q48.1 (D), R262.1
unnamed: C332.2, DD33.16 (VBATS), R256.2, R261.1
unnamed: C339.1, DD33.24 (VCC), DD33.25 (VDRV)
unnamed: C364.1, DD37.6 (ACIN)
unnamed: C366.2, DD37.13 (ADIN), R296.2
unnamed: C351.2, DD37.30 (BT1)
unnamed: C350.2, DD37.20 (BT2)
unnamed: C367.1, DD37.15 (COMP), R297.1
unnamed: DD37.29 (HD1), R288.2
unnamed: DD37.21 (HD2), R291.2
unnamed: DD37.27 (LD1), R287.2
unnamed: DD37.23 (LD2), R292.2
unnamed: C357.2, DD37.32 (SNS1N), R282.2
unnamed: C357.1, DD37.1 (SNS1P), R283.2
unnamed: C359.2, DD37.17 (SNS2N), R280.2
unnamed: C359.1, DD37.18 (SNS2P), R281.2
unnamed: C351.1, DD37.28 (SW1), L16.1, Q50.3 (S), Q51.1 (D), R286.1
unnamed: C350.1, DD37.22 (SW2), L16.2, Q49.3 (S), Q52.1 (D), R285.1
unnamed: C358.2, DD37.16 (VBATS), R279.2, R284.1
unnamed: C365.1, DD37.24 (VCC), DD37.25 (VDRV)
unnamed: C388.1, DD38.6 (ACIN)
unnamed: C390.2, DD38.13 (ADIN), R317.2
unnamed: C375.2, DD38.30 (BT1)
unnamed: C374.2, DD38.20 (BT2)
unnamed: C391.1, DD38.15 (COMP), R318.1
unnamed: DD38.29 (HD1), R309.2
unnamed: DD38.21 (HD2), R312.2
unnamed: DD38.27 (LD1), R308.2
unnamed: DD38.23 (LD2), R313.2
unnamed: C381.2, DD38.32 (SNS1N), R303.2
unnamed: C381.1, DD38.1 (SNS1P), R304.2
unnamed: C383.2, DD38.17 (SNS2N), R301.2
unnamed: C383.1, DD38.18 (SNS2P), R302.2
unnamed: C375.1, DD38.28 (SW1), L17.1, Q54.3 (S), Q55.1 (D), R307.1
unnamed: C374.1, DD38.22 (SW2), L17.2, Q53.3 (S), Q56.1 (D), R306.1
unnamed: C382.2, DD38.16 (VBATS), R300.2, R305.1
unnamed: C389.1, DD38.24 (VCC), DD38.25 (VDRV)
unnamed: C414.1, DD42.6 (ACIN)
unnamed: C416.2, DD42.13 (ADIN), R340.2
unnamed: C401.2, DD42.30 (BT1)
unnamed: C400.2, DD42.20 (BT2)
unnamed: C417.1, DD42.15 (COMP), R341.1
unnamed: DD42.29 (HD1), R332.2
unnamed: DD42.21 (HD2), R335.2
unnamed: DD42.27 (LD1), R331.2
unnamed: DD42.23 (LD2), R336.2
unnamed: C407.2, DD42.32 (SNS1N), R326.2
unnamed: C407.1, DD42.1 (SNS1P), R327.2
unnamed: C409.2, DD42.17 (SNS2N), R324.2
unnamed: C409.1, DD42.18 (SNS2P), R325.2
unnamed: C401.1, DD42.28 (SW1), L18.1, Q58.3 (S), Q59.1 (D), R330.1
unnamed: C400.1, DD42.22 (SW2), L18.2, Q57.3 (S), Q60.1 (D), R329.1
unnamed: C408.2, DD42.16 (VBATS), R323.2, R328.1
unnamed: C415.1, DD42.24 (VCC), DD42.25 (VDRV)
unnamed: C438.1, DD43.6 (ACIN)
unnamed: C440.2, DD43.13 (ADIN), R361.2
unnamed: C425.2, DD43.30 (BT1)
unnamed: C424.2, DD43.20 (BT2)
unnamed: C441.1, DD43.15 (COMP), R362.1
unnamed: DD43.29 (HD1), R353.2
unnamed: DD43.21 (HD2), R356.2
unnamed: DD43.27 (LD1), R352.2
unnamed: DD43.23 (LD2), R357.2
unnamed: C431.2, DD43.32 (SNS1N), R347.2
unnamed: C431.1, DD43.1 (SNS1P), R348.2
unnamed: C433.2, DD43.17 (SNS2N), R345.2
unnamed: C433.1, DD43.18 (SNS2P), R346.2
unnamed: C425.1, DD43.28 (SW1), L19.1, Q62.3 (S), Q63.1 (D), R351.1
unnamed: C424.1, DD43.22 (SW2), L19.2, Q61.3 (S), Q64.1 (D), R350.1
unnamed: C432.2, DD43.16 (VBATS), R344.2, R349.1
unnamed: C439.1, DD43.24 (VCC), DD43.25 (VDRV)
unnamed: C464.1, DD47.6 (ACIN)
unnamed: C466.2, DD47.13 (ADIN), R384.2
unnamed: C451.2, DD47.30 (BT1)
unnamed: C450.2, DD47.20 (BT2)
unnamed: C467.1, DD47.15 (COMP), R385.1
unnamed: DD47.29 (HD1), R376.2
unnamed: DD47.21 (HD2), R379.2
unnamed: DD47.27 (LD1), R375.2
unnamed: DD47.23 (LD2), R380.2
unnamed: C457.2, DD47.32 (SNS1N), R370.2
unnamed: C457.1, DD47.1 (SNS1P), R371.2
unnamed: C459.2, DD47.17 (SNS2N), R368.2
unnamed: C459.1, DD47.18 (SNS2P), R369.2
unnamed: C451.1, DD47.28 (SW1), L20.1, Q66.3 (S), Q67.1 (D), R374.1
unnamed: C450.1, DD47.22 (SW2), L20.2, Q65.3 (S), Q68.1 (D), R373.1
unnamed: C458.2, DD47.16 (VBATS), R367.2, R372.1
unnamed: C465.1, DD47.24 (VCC), DD47.25 (VDRV)
unnamed: C488.1, DD48.6 (ACIN)
unnamed: C490.2, DD48.13 (ADIN), R405.2
unnamed: C475.2, DD48.30 (BT1)
unnamed: C474.2, DD48.20 (BT2)
unnamed: C491.1, DD48.15 (COMP), R406.1
unnamed: DD48.29 (HD1), R397.2
unnamed: DD48.21 (HD2), R400.2
unnamed: DD48.27 (LD1), R396.2
unnamed: DD48.23 (LD2), R401.2
unnamed: C481.2, DD48.32 (SNS1N), R391.2
unnamed: C481.1, DD48.1 (SNS1P), R392.2
unnamed: C483.2, DD48.17 (SNS2N), R389.2
unnamed: C483.1, DD48.18 (SNS2P), R390.2
unnamed: C475.1, DD48.28 (SW1), L21.1, Q70.3 (S), Q71.1 (D), R395.1
unnamed: C474.1, DD48.22 (SW2), L21.2, Q69.3 (S), Q72.1 (D), R394.1
unnamed: C482.2, DD48.16 (VBATS), R388.2, R393.1
unnamed: C489.1, DD48.24 (VCC), DD48.25 (VDRV)
unnamed: C514.1, DD52.6 (ACIN)
unnamed: C516.2, DD52.13 (ADIN), R428.2
unnamed: C501.2, DD52.30 (BT1)
unnamed: C500.2, DD52.20 (BT2)
unnamed: C517.1, DD52.15 (COMP), R429.1
unnamed: DD52.29 (HD1), R420.2
unnamed: DD52.21 (HD2), R423.2
unnamed: DD52.27 (LD1), R419.2
unnamed: DD52.23 (LD2), R424.2
unnamed: C507.2, DD52.32 (SNS1N), R414.2
unnamed: C507.1, DD52.1 (SNS1P), R415.2
unnamed: C509.2, DD52.17 (SNS2N), R412.2
unnamed: C509.1, DD52.18 (SNS2P), R413.2
unnamed: C501.1, DD52.28 (SW1), L22.1, Q74.3 (S), Q75.1 (D), R418.1
unnamed: C500.1, DD52.22 (SW2), L22.2, Q73.3 (S), Q76.1 (D), R417.1
unnamed: C508.2, DD52.16 (VBATS), R411.2, R416.1
unnamed: C515.1, DD52.24 (VCC), DD52.25 (VDRV)
unnamed: C538.1, DD53.6 (ACIN)
unnamed: C540.2, DD53.13 (ADIN), R449.2
unnamed: C525.2, DD53.30 (BT1)
unnamed: C524.2, DD53.20 (BT2)
unnamed: C541.1, DD53.15 (COMP), R450.1
unnamed: DD53.29 (HD1), R441.2
unnamed: DD53.21 (HD2), R444.2
unnamed: DD53.27 (LD1), R440.2
unnamed: DD53.23 (LD2), R445.2
unnamed: C531.2, DD53.32 (SNS1N), R435.2
unnamed: C531.1, DD53.1 (SNS1P), R436.2
unnamed: C533.2, DD53.17 (SNS2N), R433.2
unnamed: C533.1, DD53.18 (SNS2P), R434.2
unnamed: C525.1, DD53.28 (SW1), L23.1, Q78.3 (S), Q79.1 (D), R439.1
unnamed: C524.1, DD53.22 (SW2), L23.2, Q77.3 (S), Q80.1 (D), R438.1
unnamed: C532.2, DD53.16 (VBATS), R432.2, R437.1
unnamed: C539.1, DD53.24 (VCC), DD53.25 (VDRV)
unnamed: C72.1, C73.1, Q5.1 (D), R34.2, R38.1
unnamed: Q5.2 (G), R48.1
unnamed: C76.1, C77.1, Q6.1 (D), R35.1, R39.1
unnamed: Q6.2 (G), R45.1
unnamed: Q7.2 (G), R44.1
unnamed: Q8.2 (G), R49.1
unnamed: C98.1, C99.1, Q9.1 (D), R57.2, R61.1
unnamed: Q9.2 (G), R71.1
unnamed: C102.1, C103.1, Q10.1 (D), R58.1, R62.1
unnamed: Q10.2 (G), R68.1
unnamed: Q11.2 (G), R67.1
unnamed: Q12.2 (G), R72.1
unnamed: C122.1, C123.1, Q13.1 (D), R78.2, R82.1
unnamed: Q13.2 (G), R92.1
unnamed: C126.1, C127.1, Q14.1 (D), R79.1, R83.1
unnamed: Q14.2 (G), R89.1
unnamed: Q15.2 (G), R88.1
unnamed: Q16.2 (G), R93.1
unnamed: C148.1, C149.1, Q17.1 (D), R101.2, R105.1
unnamed: Q17.2 (G), R115.1
unnamed: C152.1, C153.1, Q18.1 (D), R102.1, R106.1
unnamed: Q18.2 (G), R112.1
unnamed: Q19.2 (G), R111.1
unnamed: Q20.2 (G), R116.1
unnamed: C172.1, C173.1, Q21.1 (D), R122.2, R126.1
unnamed: Q21.2 (G), R136.1
unnamed: C176.1, C177.1, Q22.1 (D), R123.1, R127.1
unnamed: Q22.2 (G), R133.1
unnamed: Q23.2 (G), R132.1
unnamed: Q24.2 (G), R137.1
unnamed: C198.1, C199.1, Q25.1 (D), R145.2, R149.1
unnamed: Q25.2 (G), R159.1
unnamed: C202.1, C203.1, Q26.1 (D), R146.1, R150.1
unnamed: Q26.2 (G), R156.1
unnamed: Q27.2 (G), R155.1
unnamed: Q28.2 (G), R160.1
unnamed: C222.1, C223.1, Q29.1 (D), R166.2, R170.1
unnamed: Q29.2 (G), R180.1
unnamed: C226.1, C227.1, Q30.1 (D), R167.1, R171.1
unnamed: Q30.2 (G), R177.1
unnamed: Q31.2 (G), R176.1
unnamed: Q32.2 (G), R181.1
unnamed: C248.1, C249.1, Q33.1 (D), R189.2, R193.1
unnamed: Q33.2 (G), R203.1
unnamed: C252.1, C253.1, Q34.1 (D), R190.1, R194.1
unnamed: Q34.2 (G), R200.1
unnamed: Q35.2 (G), R199.1
unnamed: Q36.2 (G), R204.1
unnamed: C272.1, C273.1, Q37.1 (D), R210.2, R214.1
unnamed: Q37.2 (G), R224.1
unnamed: C276.1, C277.1, Q38.1 (D), R211.1, R215.1
unnamed: Q38.2 (G), R221.1
unnamed: Q39.2 (G), R220.1
unnamed: Q40.2 (G), R225.1
unnamed: C298.1, C299.1, Q41.1 (D), R233.2, R237.1
unnamed: Q41.2 (G), R247.1
unnamed: C302.1, C303.1, Q42.1 (D), R234.1, R238.1
unnamed: Q42.2 (G), R244.1
unnamed: Q43.2 (G), R243.1
unnamed: Q44.2 (G), R248.1
unnamed: C322.1, C323.1, Q45.1 (D), R254.2, R258.1
unnamed: Q45.2 (G), R268.1
unnamed: C326.1, C327.1, Q46.1 (D), R255.1, R259.1
unnamed: Q46.2 (G), R265.1
unnamed: Q47.2 (G), R264.1
unnamed: Q48.2 (G), R269.1
unnamed: C348.1, C349.1, Q49.1 (D), R277.2, R281.1
unnamed: Q49.2 (G), R291.1
unnamed: C352.1, C353.1, Q50.1 (D), R278.1, R282.1
unnamed: Q50.2 (G), R288.1
unnamed: Q51.2 (G), R287.1
unnamed: Q52.2 (G), R292.1
unnamed: C372.1, C373.1, Q53.1 (D), R298.2, R302.1
unnamed: Q53.2 (G), R312.1
unnamed: C376.1, C377.1, Q54.1 (D), R299.1, R303.1
unnamed: Q54.2 (G), R309.1
unnamed: Q55.2 (G), R308.1
unnamed: Q56.2 (G), R313.1
unnamed: C398.1, C399.1, Q57.1 (D), R321.2, R325.1
unnamed: Q57.2 (G), R335.1
unnamed: C402.1, C403.1, Q58.1 (D), R322.1, R326.1
unnamed: Q58.2 (G), R332.1
unnamed: Q59.2 (G), R331.1
unnamed: Q60.2 (G), R336.1
unnamed: C422.1, C423.1, Q61.1 (D), R342.2, R346.1
unnamed: Q61.2 (G), R356.1
unnamed: C426.1, C427.1, Q62.1 (D), R343.1, R347.1
unnamed: Q62.2 (G), R353.1
unnamed: Q63.2 (G), R352.1
unnamed: Q64.2 (G), R357.1
unnamed: C448.1, C449.1, Q65.1 (D), R365.2, R369.1
unnamed: Q65.2 (G), R379.1
unnamed: C452.1, C453.1, Q66.1 (D), R366.1, R370.1
unnamed: Q66.2 (G), R376.1
unnamed: Q67.2 (G), R375.1
unnamed: Q68.2 (G), R380.1
unnamed: C472.1, C473.1, Q69.1 (D), R386.2, R390.1
unnamed: Q69.2 (G), R400.1
unnamed: C476.1, C477.1, Q70.1 (D), R387.1, R391.1
unnamed: Q70.2 (G), R397.1
unnamed: Q71.2 (G), R396.1
unnamed: Q72.2 (G), R401.1
unnamed: C498.1, C499.1, Q73.1 (D), R409.2, R413.1
unnamed: Q73.2 (G), R423.1
unnamed: C502.1, C503.1, Q74.1 (D), R410.1, R414.1
unnamed: Q74.2 (G), R420.1
unnamed: Q75.2 (G), R419.1
unnamed: Q76.2 (G), R424.1
unnamed: C522.1, C523.1, Q77.1 (D), R430.2, R434.1
unnamed: Q77.2 (G), R444.1
unnamed: C526.1, C527.1, Q78.1 (D), R431.1, R435.1
unnamed: Q78.2 (G), R441.1
unnamed: Q79.2 (G), R440.1
unnamed: Q80.2 (G), R445.1
unnamed: R53.1, TP4.1
unnamed: R76.1, TP6.1
unnamed: R97.1, TP8.1
unnamed: R120.1, TP10.1
unnamed: R141.1, TP12.1
unnamed: R164.1, TP14.1
unnamed: R185.1, TP16.1
unnamed: R208.1, TP18.1
unnamed: R229.1, TP20.1
unnamed: R252.1, TP22.1
unnamed: R273.1, TP24.1
unnamed: R296.1, TP26.1
unnamed: R317.1, TP28.1
unnamed: R340.1, TP30.1
unnamed: R361.1, TP32.1
unnamed: R384.1, TP34.1
unnamed: R405.1, TP36.1
unnamed: R428.1, TP38.1
unnamed: R449.1, TP40.1

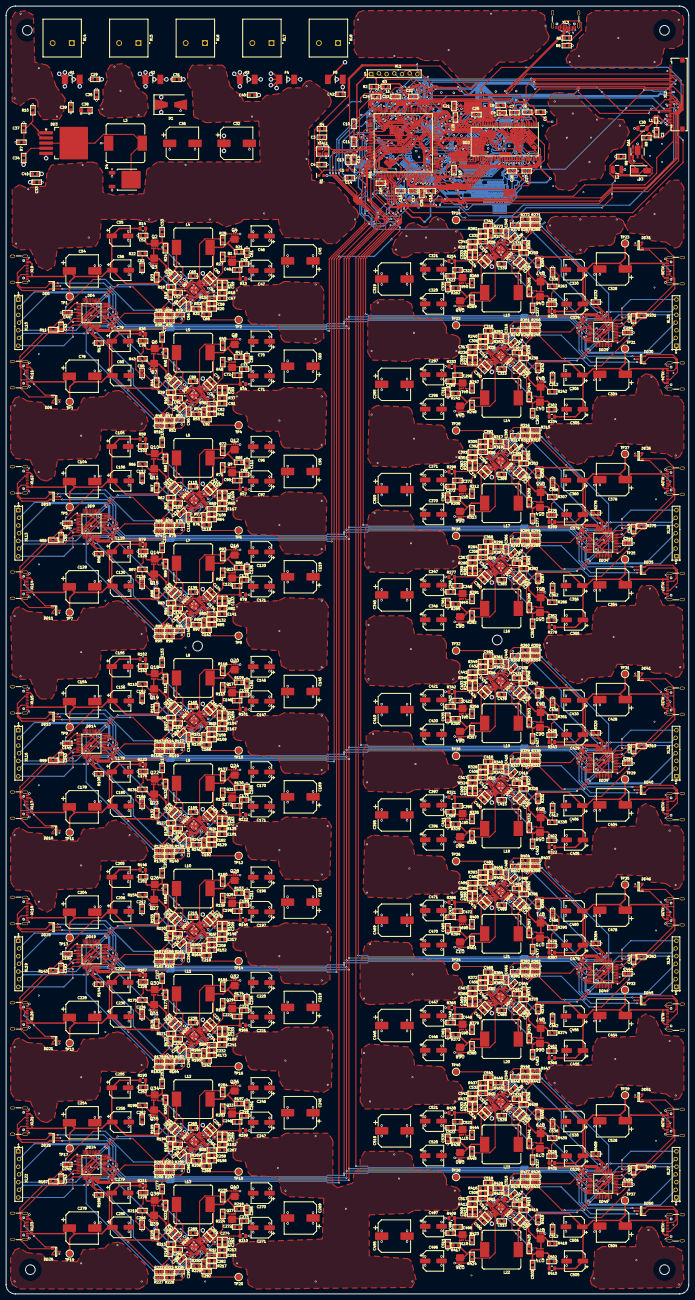
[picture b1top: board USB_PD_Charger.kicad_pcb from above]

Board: 4 copper layers, 225.6 x 425.6 mm, 1242 parts (0 on the bottom side), 852 nets.
